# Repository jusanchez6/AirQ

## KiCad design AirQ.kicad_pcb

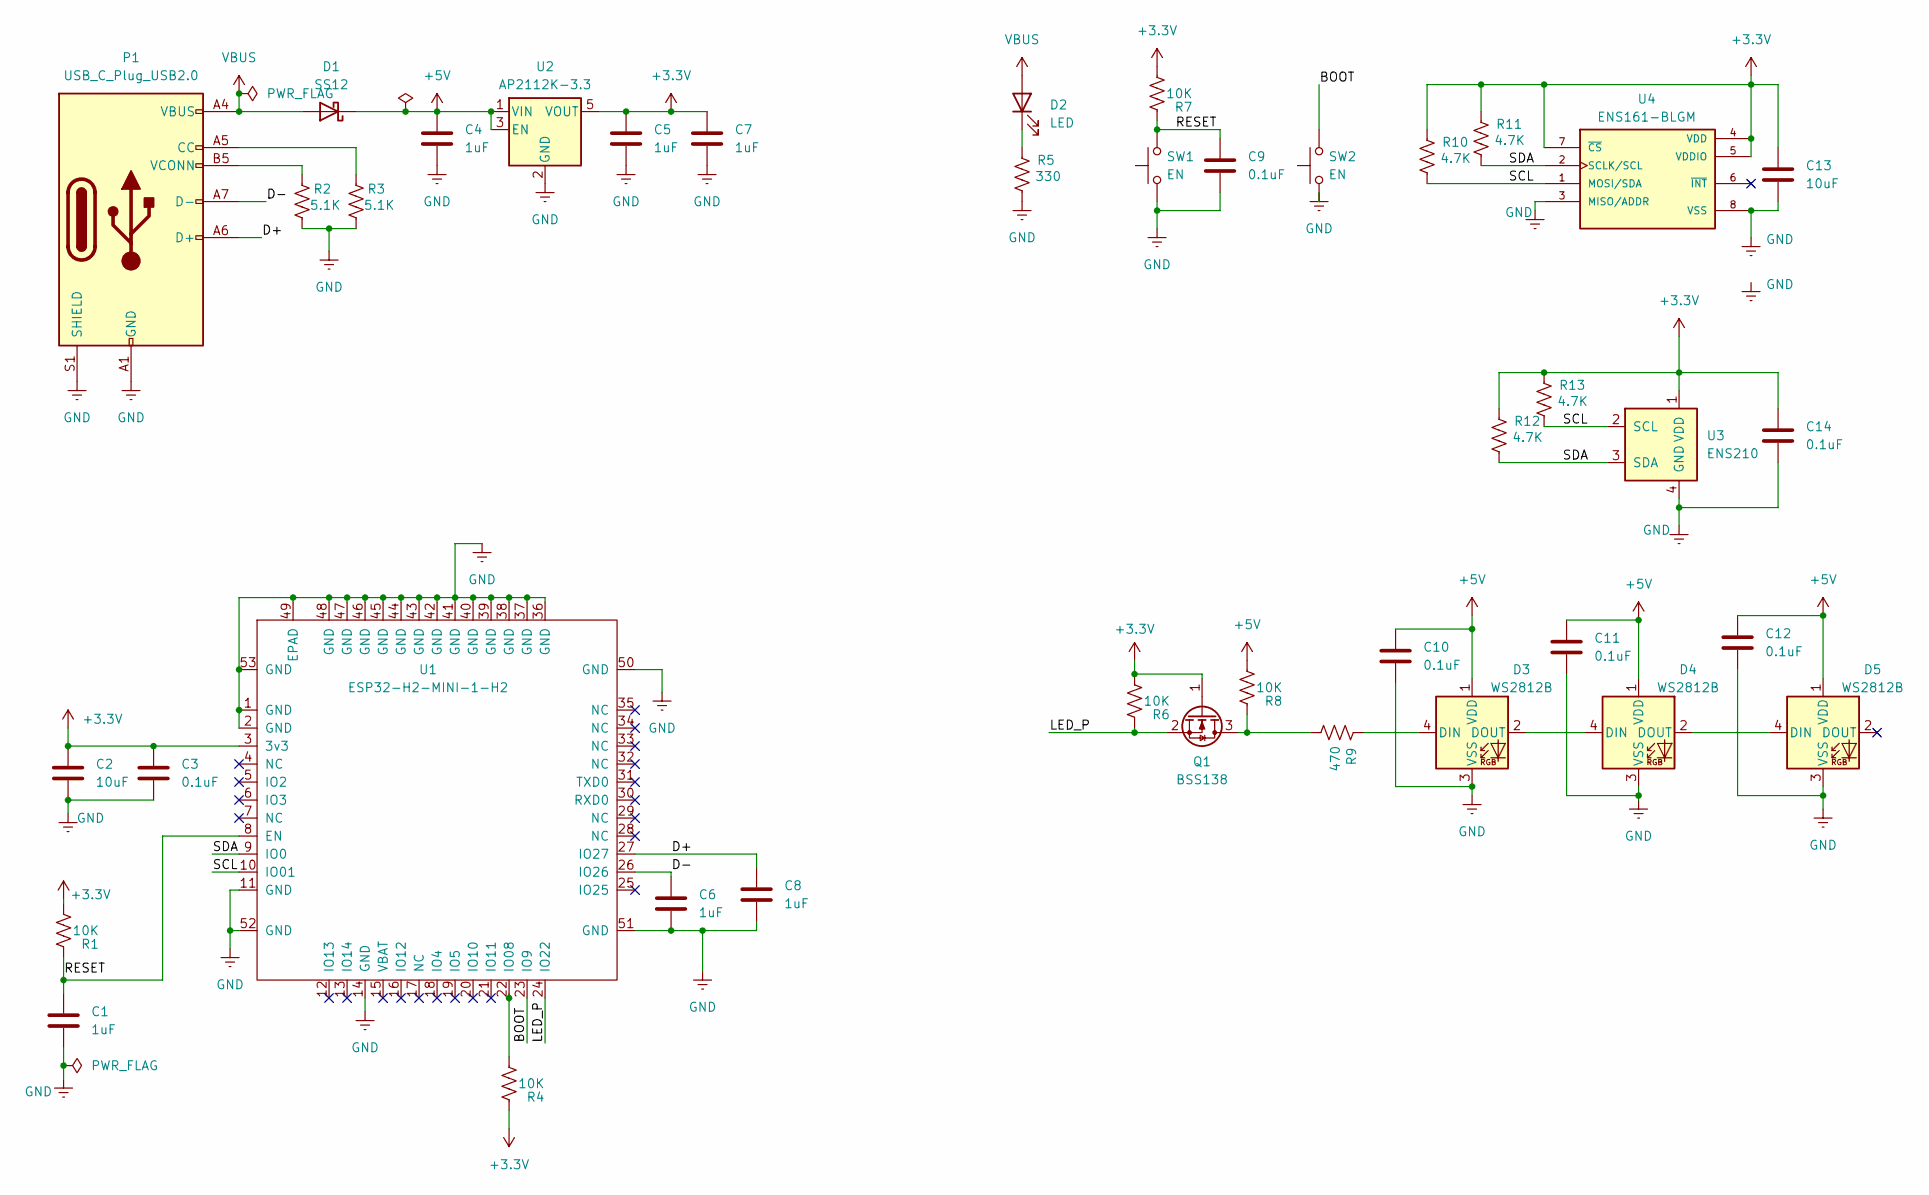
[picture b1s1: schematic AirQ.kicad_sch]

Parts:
C1, C4, C5, C6, C7, C8: 1uF; C_0201_0603Metric; DigiKey Part Number 541-0.0JTR-ND
C2, C13: 10uF; C_0402_1005Metric; DigiKey Part Number 490-GRM155R60J106ME05DCT-ND
C3, C9, C10, C11, C12, C14: 0.1uF; C_0402_1005Metric; DigiKey Part Number 1276-1002-6-ND
D1: SS12; D_SMA; DigiKey Part Number 1801-SS12TR-ND
D2: LED; LED_0603_1608Metric; DigiKey Part Number SML-D12U1WT86CT-ND
D3, D4, D5: WS2812B; LED_WS2812B_PLCC4_5.0x5.0mm_P3.2mm; DigiKey Part Number 1568-16347CT-ND
P1: USB_C_Plug_USB2.0; USB_C_Receptacle_GCT_USB4105-xx-A_16P_TopMnt_Horizontal; DigiKey Part Number 2223-UJ20-C-H-G-SMT-1-P16-TR-ND
Q1: BSS138; SOT-23; DigiKey Part Number BSS138CT-ND
R1, R4, R6, R7, R8: 10K; R_0402_1005Metric; DigiKey Part Number 541-M55342K11B10E0RS3CT-ND
R2, R3: 5.1K; R_1206_3216Metric_Pad1.30x1.75mm_HandSolder; DigiKey Part Number 541-D55342K07B5H10RS2CT-ND
R5: 330; R_0805_2012Metric; DigiKey Part Number 541-M55342K06B330GRS2CT-ND
R9: 470; R_1206_3216Metric; DigiKey Part Number 541-D55342K07B470GRS2CT-ND
R10, R11, R12, R13: 4.7K; R_0805_2012Metric; DigiKey Part Number 541-M55342K06B4H70RS2CT-ND
SW1, SW2: EN; SW_Push_1P1T_NO_CK_KMR2
U1: ESP32-H2-MINI-1-H2; ESP32-C6-MINI-1; DigiKey Part Number 1965-ESP32-H2-MINI-1-H2SCT-ND
U2: AP2112K-3.3; SOT-23-5; DigiKey Part Number AP2112K-3.3TRG1DICT-ND
U3: ENS210; AMS_QFN-4-1EP_2x2mm_P0.95mm_EP0.7x1.6mm; DigiKey Part Number 2618-ENS210-LQFMCT-ND
U4: ENS161-BLGM; XDCR_ENS161-BLGM; DigiKey Part Number 2618-ENS161-BLGTCT-ND

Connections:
+3.3V: C2.1, C3.1, C5.1, C7.1, C13.1, C14.1, Q1.1 (G), R1.2, R4.1, R6.2, R7.2, R10.1, R11.1, R12.1, R13.1, U1.3 (3v3), U2.5 (VOUT), U3.1 (VDD), U4.4 (VDD), U4.5 (VDDIO), U4.7 (~CS)
+5V: C4.1, C10.1, C11.1, C12.1, D1.1 (K), D3.1 (VDD), D4.1 (VDD), D5.1 (VDD), R8.2, U2.1 (VIN), U2.3 (EN)
/BOOT: SW2.2, U1.23 (IO9)
/D+: C8.1, P1.A6 (D+), U1.27 (IO27)
/D-: C6.1, P1.A7 (D-), U1.26 (IO26)
/LED_P: Q1.2 (S), R6.1, U1.24 (IO22)
/RESET: C1.1, C9.1, R1.1, R7.1, SW1.2, U1.8 (EN)
/SCL: R10.2, R13.2, U1.10 (IO01), U3.2 (SCL), U4.1 (MOSI/SDA)
/SDA: R11.2, R12.2, U1.9 (IO0), U3.3 (SDA), U4.2 (SCLK/SCL)
GND: C1.2, C2.2, C3.2, C4.2, C5.2, C6.2, C7.2, C8.2, C9.2, C10.2, C11.2, C12.2, C13.2, C14.2, D3.3 (VSS), D4.3 (VSS), D5.3 (VSS), P1.A1 (GND), P1.A12 (GND), P1.B1 (GND), P1.B12 (GND), P1.S1 (SHIELD), R2.2, R3.2, R5.2, SW1.1, SW2.1, U1.1 (GND), U1.2 (GND), U1.11 (GND), U1.14 (GND), U1.36 (GND), U1.37 (GND), U1.38 (GND), U1.39 (GND), U1.40 (GND), U1.41 (GND), U1.42 (GND), U1.43 (GND), U1.44 (GND), U1.45 (GND), U1.46 (GND), U1.47 (GND), U1.48 (GND), U1.49 (EPAD), U1.50 (GND), U1.51 (GND), U1.52 (GND), U1.53 (GND), U2.2 (GND), U3.4 (GND), U3.5 (GND), U4.3 (MISO/ADDR), U4.8 (VSS), U4.9 (VSS)
unnamed: D2.1 (K), R5.1
unnamed: D3.4 (DIN), R9.1
unnamed: D3.2 (DOUT), D4.4 (DIN)
unnamed: D4.2 (DOUT), D5.4 (DIN)
unnamed: P1.A5 (CC), R3.1
unnamed: P1.B5 (VCONN), R2.1
unnamed: Q1.3 (D), R8.1, R9.2
unnamed: R4.2, U1.22 (IO08)
VBUS: D1.2 (A), D2.2 (A), P1.A4 (VBUS), P1.A9 (VBUS), P1.B4 (VBUS), P1.B9 (VBUS)

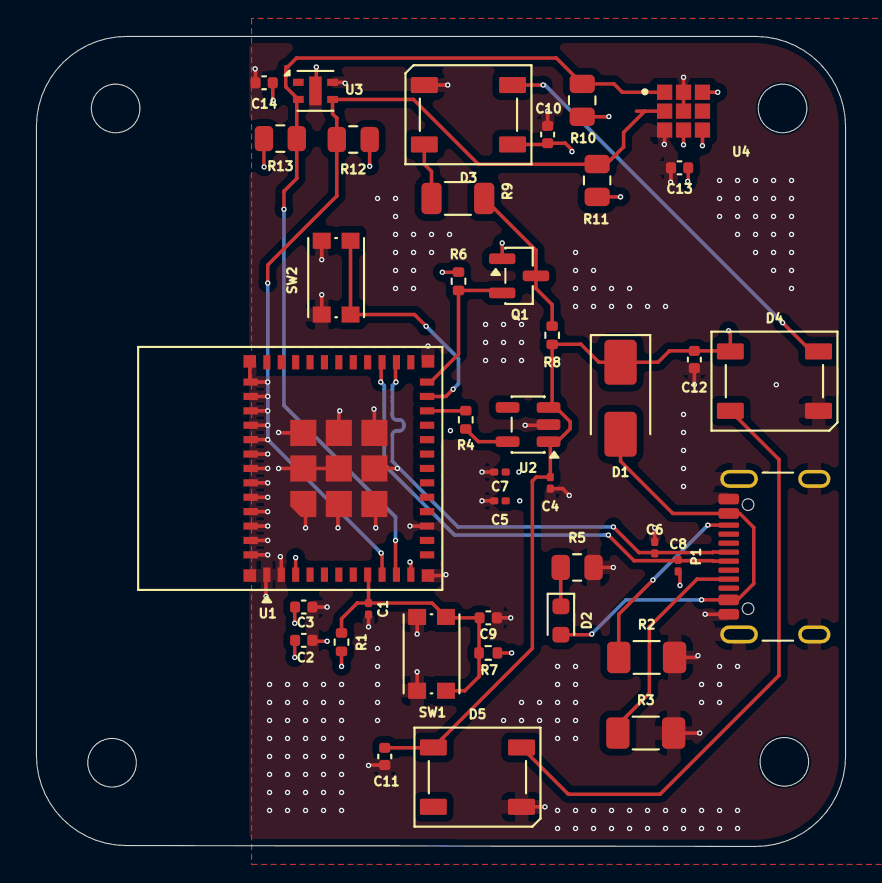
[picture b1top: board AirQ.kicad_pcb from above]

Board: 4 copper layers, 44.9 x 45.0 mm, 40 parts (0 on the bottom side), 19 nets.

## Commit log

2026-06-25 Add: Project Files
2026-06-25 Feature: avances esquematico
2026-06-26 Avances Viernes
2026-06-28 agujeros para la pcb
